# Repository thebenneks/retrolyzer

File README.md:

# RetroLyzer
FPGA Board for a 64-Bit LogicAnalyzer plus a board that allows hacking of a MC68000P10 by plugging it into the logic analyzer board. Thus other Retro CPUs can be hacked :-)

The orginal idea was to build a logicanalyzer and as I came across some retro computing and remembered the fun I had with 68K CPUs I extended the original design by a socket for a MC68000P10 64 DIP. 

The goal is to add bus transceivers for level shifting of the 5V TTL world to the 3.3V LVTTL world that the Spartan 6 can handle. I also add a 512K * 16 Bit SRAM which gets routed through the FPGA and the bus transceivers. 

plus 

using 

resulting into something like this 

# LogicAnalyzer Board

[LogicAnalyzer Details](kicad/logicanalyzer/README.md)

# Retro MC68k-HackingBoard

[MC68000P10 Details](kicad/mc68000board/README.md)

stay tuned .. more to come :-)

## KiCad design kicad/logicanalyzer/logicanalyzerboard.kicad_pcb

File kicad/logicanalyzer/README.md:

# LogicAnalyzer Board 
This folder holds the Kicad project for the PCB

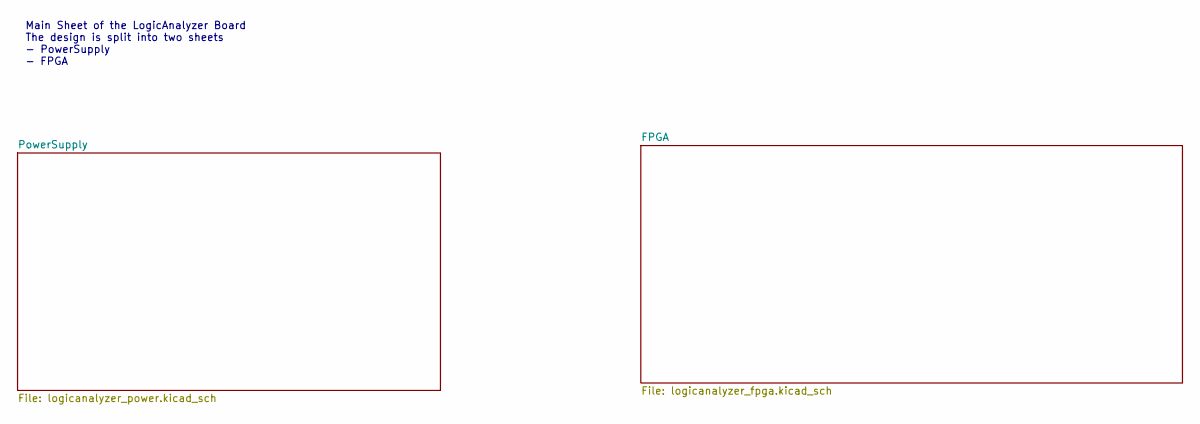
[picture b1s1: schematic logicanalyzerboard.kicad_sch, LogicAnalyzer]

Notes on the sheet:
Main Sheet of the LogicAnalyzer Board The design is split into two sheets - PowerSupply - FPGA

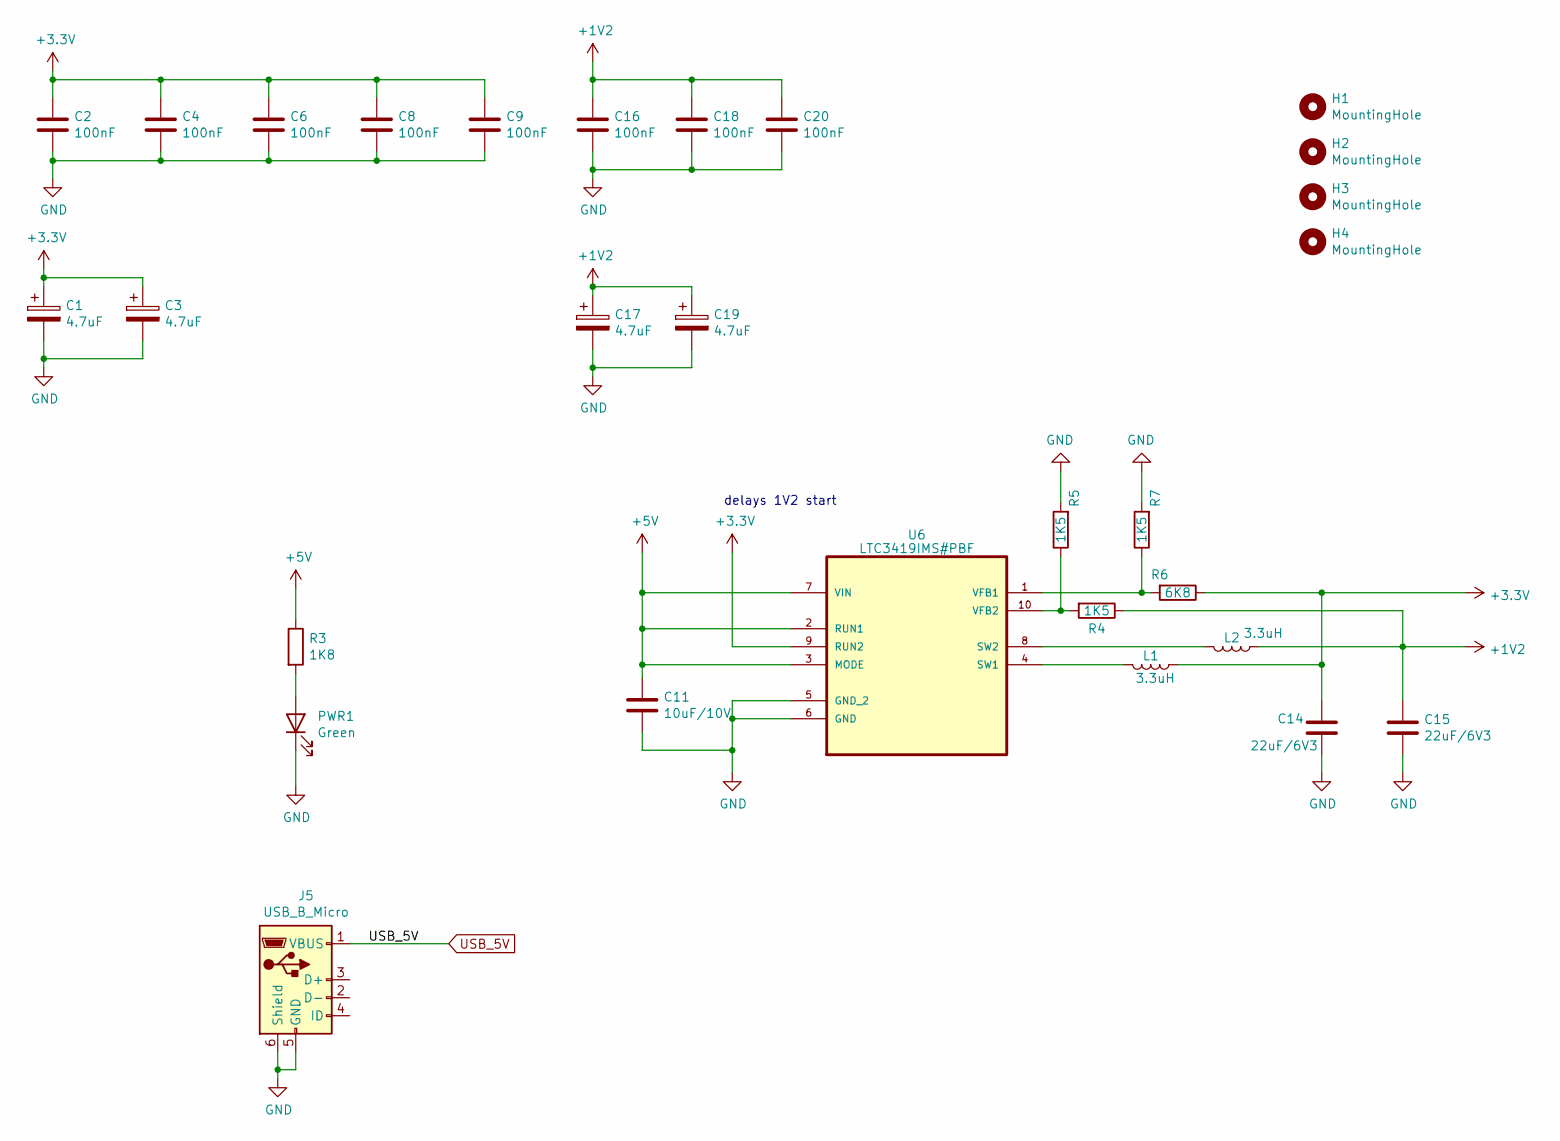
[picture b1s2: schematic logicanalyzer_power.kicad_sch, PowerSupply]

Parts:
C1, C3, C17, C19: 4.7uF; C_0805_2012Metric
C2, C4, C6, C8, C9, C16, C18, C20: 100nF; C_0603_1608Metric
C11: 10uF/10V; C_0805_2012Metric
C14, C15: 22uF/6V3; C_0805_2012Metric
H1, H2, H3, H4: MountingHole; MountingHole3mmInclPaste
J5: USB_B_Micro; USB_Micro-B_Molex-105017-0001
L1, L2: 3.3uH; L_6.3x6.3_H3
PWR1: Green; LED_1206_3216Metric
R3: 1K8; R_0805_2012Metric
R4, R5, R7: 1K5; R_0805_2012Metric
R6: 6K8; R_0805_2012Metric
U6: LTC3419IMS#PBF; SOP50P490X110-10N; MPN LTC3419IMS#PBF

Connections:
+1V2: C15.1, C16.1, C17.1, C18.1, C19.1, C20.1, L2.1, R4.1; also elsewhere on the board
+3V3: C1.1, C2.1, C3.1, C4.1, C6.1, C8.1, C9.1, C14.1, L1.1, R6.1, U6.9 (RUN2); also elsewhere on the board
+5V: C11.1, R3.1, U6.2 (RUN1), U6.3 (MODE), U6.7 (VIN)
GND: C1.2, C2.2, C3.2, C4.2, C6.2, C8.2, C9.2, C11.2, C14.2, C15.2, C16.2, C17.2, C18.2, C19.2, C20.2, J5.5 (GND), J5.6 (Shield), PWR1.1 (K), R5.2, R7.2, U6.5 (GND_2), U6.6 (GND); also elsewhere on the board
unnamed: PWR1.2 (A), R3.2
unnamed: L1.2, U6.4 (SW1)
unnamed: L2.2, U6.8 (SW2)
unnamed: R6.2, R7.1, U6.1 (VFB1)
unnamed: R4.2, R5.1, U6.10 (VFB2)
USB_5V: J5.1 (VBUS)

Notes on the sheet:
delays 1V2 start

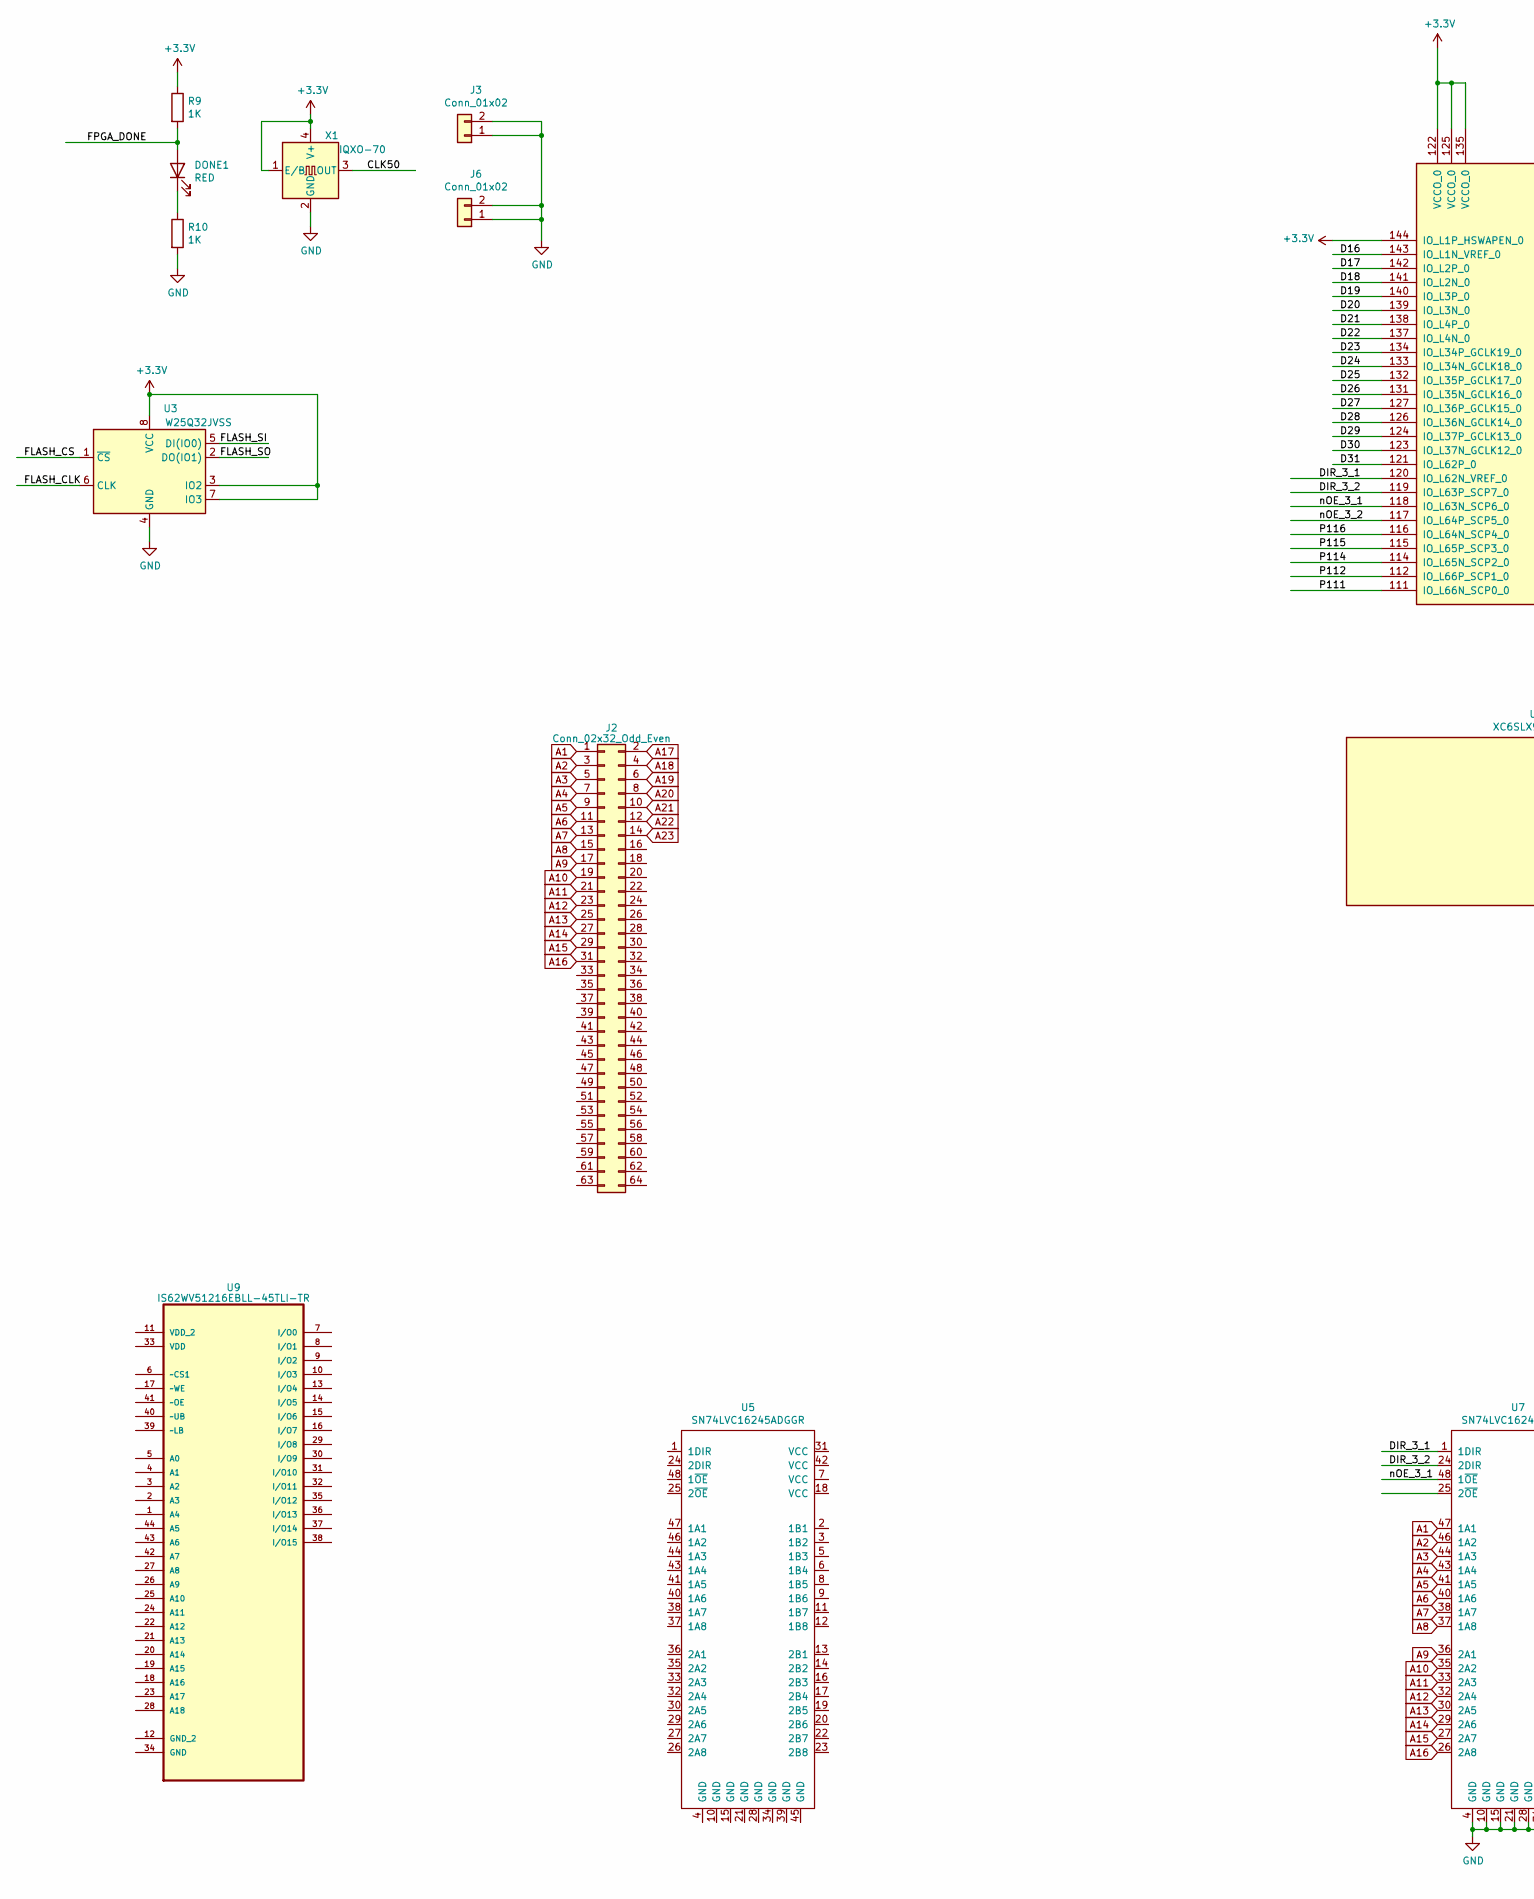
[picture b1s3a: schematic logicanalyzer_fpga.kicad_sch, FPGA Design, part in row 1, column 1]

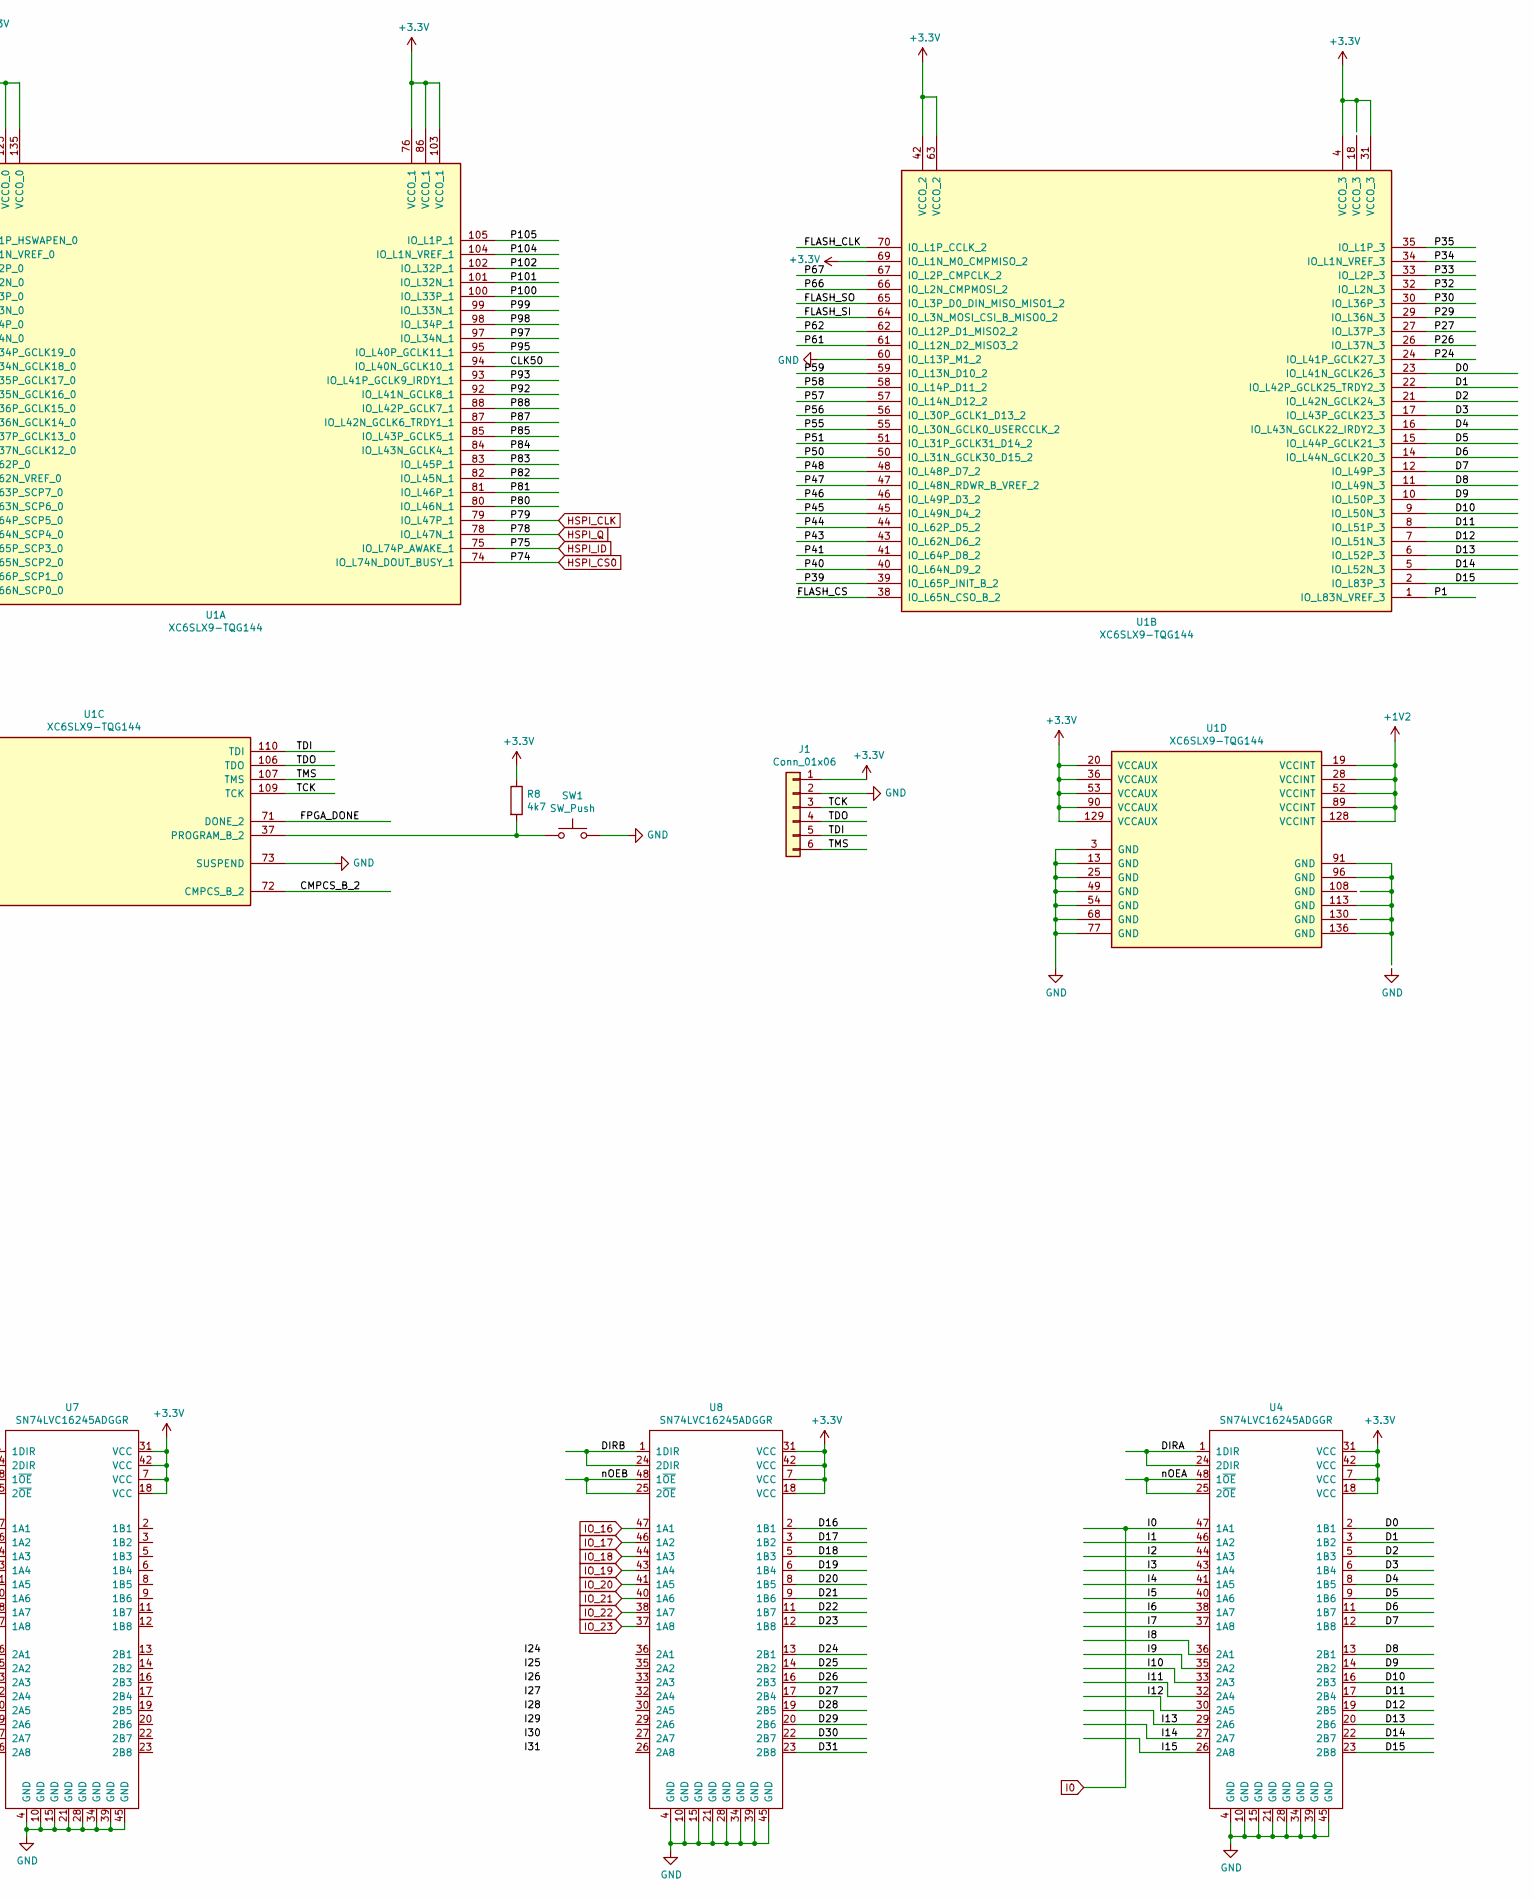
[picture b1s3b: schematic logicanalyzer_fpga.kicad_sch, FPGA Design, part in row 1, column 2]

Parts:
DONE1: RED; LED_1206_3216Metric
J1: Conn_01x06; PinHeader_1x06_P2.54mm_Vertical
J2: Conn_02x32_Odd_Even; PinSocket_2x32_P2.54mm_Vertical
J3, J6: Conn_01x02; PinHeader_1x02_P2.54mm_Vertical
R8: 4k7; R_0805_2012Metric
R9, R10: 1K; R_0805_2012Metric
SW1: SW_Push; SW_DIP_SPSTx01_Slide_6.7x4.1mm_W8.61mm_P2.54mm_LowProfile
U1: XC6SLX9-TQG144; LQFP-144_20x20mm_P0.5mm
U3: W25Q32JVSS; SOIC-8_5.23x5.23mm_P1.27mm
U4, U5, U7, U8: SN74LVC16245ADGGR; TSSOP-48_6.1x12.5mm_P0.5mm
U9: IS62WV51216EBLL-45TLI-TR; IS62WV51216-TSOP-44N; MPN IS62WV51216EBLL-45TLI-TR
X1: IQXO-70; Oscillator_SMD_IQD_IQXO70-4Pin_7.5x5.0mm

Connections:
+1V2: U1.19 (VCCINT), U1.28 (VCCINT), U1.52 (VCCINT), U1.89 (VCCINT), U1.128 (VCCINT); also elsewhere on the board
+3V3: J1.1, R8.1, R9.1, U1.4 (VCCO_3), U1.20 (VCCAUX), U1.31 (VCCO_3), U1.36 (VCCAUX), U1.42 (VCCO_2), U1.53 (VCCAUX), U1.63 (VCCO_2), U1.69 (IO_L1N_M0_CMPMISO_2), U1.76 (VCCO_1), U1.86 (VCCO_1), U1.90 (VCCAUX), U1.103 (VCCO_1), U1.122 (VCCO_0), U1.125 (VCCO_0), U1.129 (VCCAUX), U1.135 (VCCO_0), U1.144 (IO_L1P_HSWAPEN_0), U3.3 (IO2), U3.7 (IO3), U3.8 (VCC), U4.7 (VCC), U4.18 (VCC), U4.31 (VCC), U4.42 (VCC), U7.7 (VCC), U7.18 (VCC), U7.31 (VCC), U7.42 (VCC), U8.7 (VCC), U8.18 (VCC), U8.31 (VCC), U8.42 (VCC), X1.1 (E/B), X1.4 (V+); also elsewhere on the board
/FPGA/CLK50: U1.94 (IO_L40N_GCLK10_1), X1.3 (OUT)
/FPGA/CMPCS_B_2: U1.72 (CMPCS_B_2)
/FPGA/D0: U1.23 (IO_L41N_GCLK26_3), U4.2 (1B1)
/FPGA/D1: U1.22 (IO_L42P_GCLK25_TRDY2_3), U4.3 (1B2)
/FPGA/D2: U1.21 (IO_L42N_GCLK24_3), U4.5 (1B3)
/FPGA/D3: U1.17 (IO_L43P_GCLK23_3), U4.6 (1B4)
/FPGA/D4: U1.16 (IO_L43N_GCLK22_IRDY2_3), U4.8 (1B5)
/FPGA/D5: U1.15 (IO_L44P_GCLK21_3), U4.9 (1B6)
/FPGA/D6: U1.14 (IO_L44N_GCLK20_3), U4.11 (1B7)
/FPGA/D7: U1.12 (IO_L49P_3), U4.12 (1B8)
/FPGA/D8: U1.11 (IO_L49N_3), U4.13 (2B1)
/FPGA/D9: U1.10 (IO_L50P_3), U4.14 (2B2)
/FPGA/D10: U1.9 (IO_L50N_3), U4.16 (2B3)
/FPGA/D11: U1.8 (IO_L51P_3), U4.17 (2B4)
/FPGA/D12: U1.7 (IO_L51N_3), U4.19 (2B5)
/FPGA/D13: U1.6 (IO_L52P_3), U4.20 (2B6)
/FPGA/D14: U1.5 (IO_L52N_3), U4.22 (2B7)
/FPGA/D15: U1.2 (IO_L83P_3), U4.23 (2B8)
/FPGA/D16: U1.143 (IO_L1N_VREF_0), U8.2 (1B1)
/FPGA/D17: U1.142 (IO_L2P_0), U8.3 (1B2)
/FPGA/D18: U1.141 (IO_L2N_0), U8.5 (1B3)
/FPGA/D19: U1.140 (IO_L3P_0), U8.6 (1B4)
/FPGA/D20: U1.139 (IO_L3N_0), U8.8 (1B5)
/FPGA/D21: U1.138 (IO_L4P_0), U8.9 (1B6)
/FPGA/D22: U1.137 (IO_L4N_0), U8.11 (1B7)
/FPGA/D23: U1.134 (IO_L34P_GCLK19_0), U8.12 (1B8)
/FPGA/D24: U1.133 (IO_L34N_GCLK18_0), U8.13 (2B1)
/FPGA/D25: U1.132 (IO_L35P_GCLK17_0), U8.14 (2B2)
/FPGA/D26: U1.131 (IO_L35N_GCLK16_0), U8.16 (2B3)
/FPGA/D27: U1.127 (IO_L36P_GCLK15_0), U8.17 (2B4)
/FPGA/D28: U1.126 (IO_L36N_GCLK14_0), U8.19 (2B5)
/FPGA/D29: U1.124 (IO_L37P_GCLK13_0), U8.20 (2B6)
/FPGA/D30: U1.123 (IO_L37N_GCLK12_0), U8.22 (2B7)
/FPGA/D31: U1.121 (IO_L62P_0), U8.23 (2B8)
/FPGA/DIRA: U4.1 (1DIR), U4.24 (2DIR)
/FPGA/DIRB: U8.1 (1DIR), U8.24 (2DIR)
/FPGA/DIR_3_1: U1.120 (IO_L62N_VREF_0), U7.1 (1DIR)
/FPGA/DIR_3_2: U1.119 (IO_L63P_SCP7_0), U7.24 (2DIR)
/FPGA/FLASH_CLK: U1.70 (IO_L1P_CCLK_2), U3.6 (CLK)
/FPGA/FLASH_CS: U1.38 (IO_L65N_CSO_B_2), U3.1 (~CS)
/FPGA/FLASH_SI: U1.64 (IO_L3N_MOSI_CSI_B_MISO0_2), U3.5 (DI(IO0))
/FPGA/FLASH_SO: U1.65 (IO_L3P_D0_DIN_MISO_MISO1_2), U3.2 (DO(IO1))
/FPGA/FPGA_DONE: DONE1.2 (A), R9.2, U1.71 (DONE_2)
/FPGA/I1: U4.46 (1A2)
/FPGA/I2: U4.44 (1A3)
/FPGA/I3: U4.43 (1A4)
/FPGA/I4: U4.41 (1A5)
/FPGA/I5: U4.40 (1A6)
/FPGA/I6: U4.38 (1A7)
/FPGA/I7: U4.37 (1A8)
/FPGA/I8: U4.36 (2A1)
/FPGA/I9: U4.35 (2A2)
/FPGA/I10: U4.33 (2A3)
/FPGA/I11: U4.32 (2A4)
/FPGA/I12: U4.30 (2A5)
/FPGA/I13: U4.29 (2A6)
/FPGA/I14: U4.27 (2A7)
/FPGA/I15: U4.26 (2A8)
/FPGA/P1: U1.1 (IO_L83N_VREF_3)
/FPGA/P24: U1.24 (IO_L41P_GCLK27_3)
/FPGA/P26: U1.26 (IO_L37N_3)
/FPGA/P27: U1.27 (IO_L37P_3)
/FPGA/P29: U1.29 (IO_L36N_3)
/FPGA/P30: U1.30 (IO_L36P_3)
/FPGA/P32: U1.32 (IO_L2N_3)
/FPGA/P33: U1.33 (IO_L2P_3)
/FPGA/P34: U1.34 (IO_L1N_VREF_3)
/FPGA/P35: U1.35 (IO_L1P_3)
/FPGA/P39: U1.39 (IO_L65P_INIT_B_2)
/FPGA/P40: U1.40 (IO_L64N_D9_2)
/FPGA/P41: U1.41 (IO_L64P_D8_2)
/FPGA/P43: U1.43 (IO_L62N_D6_2)
/FPGA/P44: U1.44 (IO_L62P_D5_2)
/FPGA/P45: U1.45 (IO_L49N_D4_2)
/FPGA/P46: U1.46 (IO_L49P_D3_2)
/FPGA/P47: U1.47 (IO_L48N_RDWR_B_VREF_2)
/FPGA/P48: U1.48 (IO_L48P_D7_2)
/FPGA/P50: U1.50 (IO_L31N_GCLK30_D15_2)
/FPGA/P51: U1.51 (IO_L31P_GCLK31_D14_2)
/FPGA/P55: U1.55 (IO_L30N_GCLK0_USERCCLK_2)
/FPGA/P56: U1.56 (IO_L30P_GCLK1_D13_2)
/FPGA/P57: U1.57 (IO_L14N_D12_2)
/FPGA/P58: U1.58 (IO_L14P_D11_2)
/FPGA/P59: U1.59 (IO_L13N_D10_2)
/FPGA/P61: U1.61 (IO_L12N_D2_MISO3_2)
/FPGA/P62: U1.62 (IO_L12P_D1_MISO2_2)
/FPGA/P66: U1.66 (IO_L2N_CMPMOSI_2)
/FPGA/P67: U1.67 (IO_L2P_CMPCLK_2)
/FPGA/P80: U1.80 (IO_L46N_1)
/FPGA/P81: U1.81 (IO_L46P_1)
/FPGA/P82: U1.82 (IO_L45N_1)
/FPGA/P83: U1.83 (IO_L45P_1)
/FPGA/P84: U1.84 (IO_L43N_GCLK4_1)
/FPGA/P85: U1.85 (IO_L43P_GCLK5_1)
/FPGA/P87: U1.87 (IO_L42N_GCLK6_TRDY1_1)
/FPGA/P88: U1.88 (IO_L42P_GCLK7_1)
/FPGA/P92: U1.92 (IO_L41N_GCLK8_1)
/FPGA/P93: U1.93 (IO_L41P_GCLK9_IRDY1_1)
/FPGA/P95: U1.95 (IO_L40P_GCLK11_1)
/FPGA/P97: U1.97 (IO_L34N_1)
/FPGA/P98: U1.98 (IO_L34P_1)
/FPGA/P99: U1.99 (IO_L33N_1)
/FPGA/P100: U1.100 (IO_L33P_1)
/FPGA/P101: U1.101 (IO_L32N_1)
/FPGA/P102: U1.102 (IO_L32P_1)
/FPGA/P104: U1.104 (IO_L1N_VREF_1)
/FPGA/P105: U1.105 (IO_L1P_1)
/FPGA/P111: U1.111 (IO_L66N_SCP0_0)
/FPGA/P112: U1.112 (IO_L66P_SCP1_0)
/FPGA/P114: U1.114 (IO_L65N_SCP2_0)
/FPGA/P115: U1.115 (IO_L65P_SCP3_0)
/FPGA/P116: U1.116 (IO_L64N_SCP4_0)
/FPGA/TCK: J1.3, U1.109 (TCK)
/FPGA/TDI: J1.5, U1.110 (TDI)
/FPGA/TDO: J1.4, U1.106 (TDO)
/FPGA/TMS: J1.6, U1.107 (TMS)
/FPGA/nOEA: U4.25 (2~OE), U4.48 (1~OE)
/FPGA/nOEB: U8.25 (2~OE), U8.48 (1~OE)
/FPGA/nOE_3_1: U1.118 (IO_L63N_SCP6_0), U7.48 (1~OE)
/FPGA/nOE_3_2: U1.117 (IO_L64P_SCP5_0)
A1: J2.1, U7.47 (1A1)
A2: J2.3, U7.46 (1A2)
A3: J2.5, U7.44 (1A3)
A4: J2.7, U7.43 (1A4)
A5: J2.9, U7.41 (1A5)
A6: J2.11, U7.40 (1A6)
A7: J2.13, U7.38 (1A7)
A8: J2.15, U7.37 (1A8)
A9: J2.17, U7.36 (2A1)
A10: J2.19, U7.35 (2A2)
A11: J2.21, U7.33 (2A3)
A12: J2.23, U7.32 (2A4)
A13: J2.25, U7.30 (2A5)
A14: J2.27, U7.29 (2A6)
A15: J2.29, U7.27 (2A7)
A16: J2.31, U7.26 (2A8)
A17: J2.2
A18: J2.4
A19: J2.6
A20: J2.8
A21: J2.10
A22: J2.12
A23: J2.14
GND: J1.2, J3.1, J3.2, J6.1, J6.2, R10.2, SW1.2, U1.3 (GND), U1.13 (GND), U1.25 (GND), U1.49 (GND), U1.54 (GND), U1.60 (IO_L13P_M1_2), U1.68 (GND), U1.73 (SUSPEND), U1.77 (GND), U3.4 (GND), U4.4 (GND), U4.10 (GND), U4.15 (GND), U4.21 (GND), U4.28 (GND), U4.34 (GND), U4.39 (GND), U4.45 (GND), U7.4 (GND), U7.10 (GND), U7.15 (GND), U7.21 (GND), U7.28 (GND), U7.34 (GND), U7.39 (GND), U7.45 (GND), U8.4 (GND), U8.10 (GND), U8.15 (GND), U8.21 (GND), U8.28 (GND), U8.34 (GND), U8.39 (GND), U8.45 (GND), X1.2 (GND); also elsewhere on the board
HSPI_CLK: U1.79 (IO_L47P_1)
HSPI_CS0: U1.74 (IO_L74N_DOUT_BUSY_1)
HSPI_ID: U1.75 (IO_L74P_AWAKE_1)
HSPI_Q: U1.78 (IO_L47N_1)
I0: U4.47 (1A1)
IO_16: U8.47 (1A1)
IO_17: U8.46 (1A2)
IO_18: U8.44 (1A3)
IO_19: U8.43 (1A4)
IO_20: U8.41 (1A5)
IO_21: U8.40 (1A6)
IO_22: U8.38 (1A7)
IO_23: U8.37 (1A8)
unnamed: DONE1.1 (K), R10.1
unnamed: R8.2, SW1.1, U1.37 (PROGRAM_B_2)
unnamed: U1.91 (GND), U1.96 (GND), U1.113 (GND), U1.136 (GND)

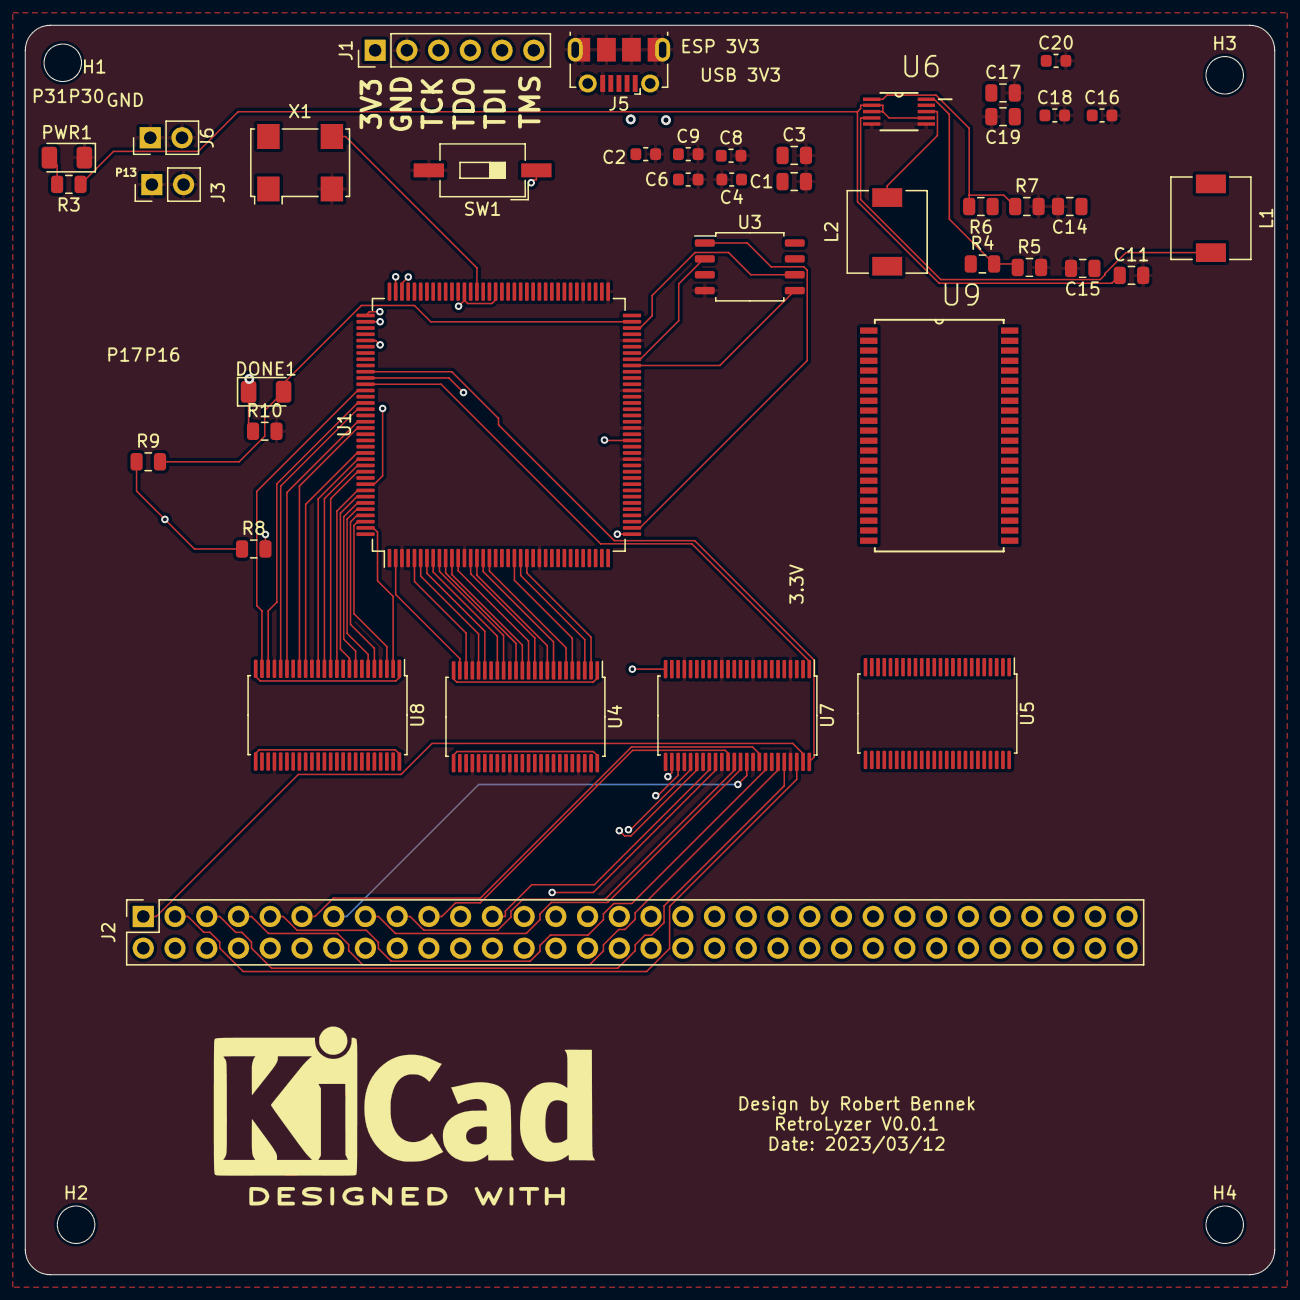
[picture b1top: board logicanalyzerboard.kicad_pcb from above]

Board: 4 copper layers, 100.0 x 100.0 mm, 46 parts (0 on the bottom side), 77 nets.

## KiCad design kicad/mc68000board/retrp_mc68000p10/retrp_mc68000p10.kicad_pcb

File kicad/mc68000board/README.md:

# MC68000P10 Board
This folder holds the Kicad project for a dedicated PCB board that can be plugged into the logic analyzer board

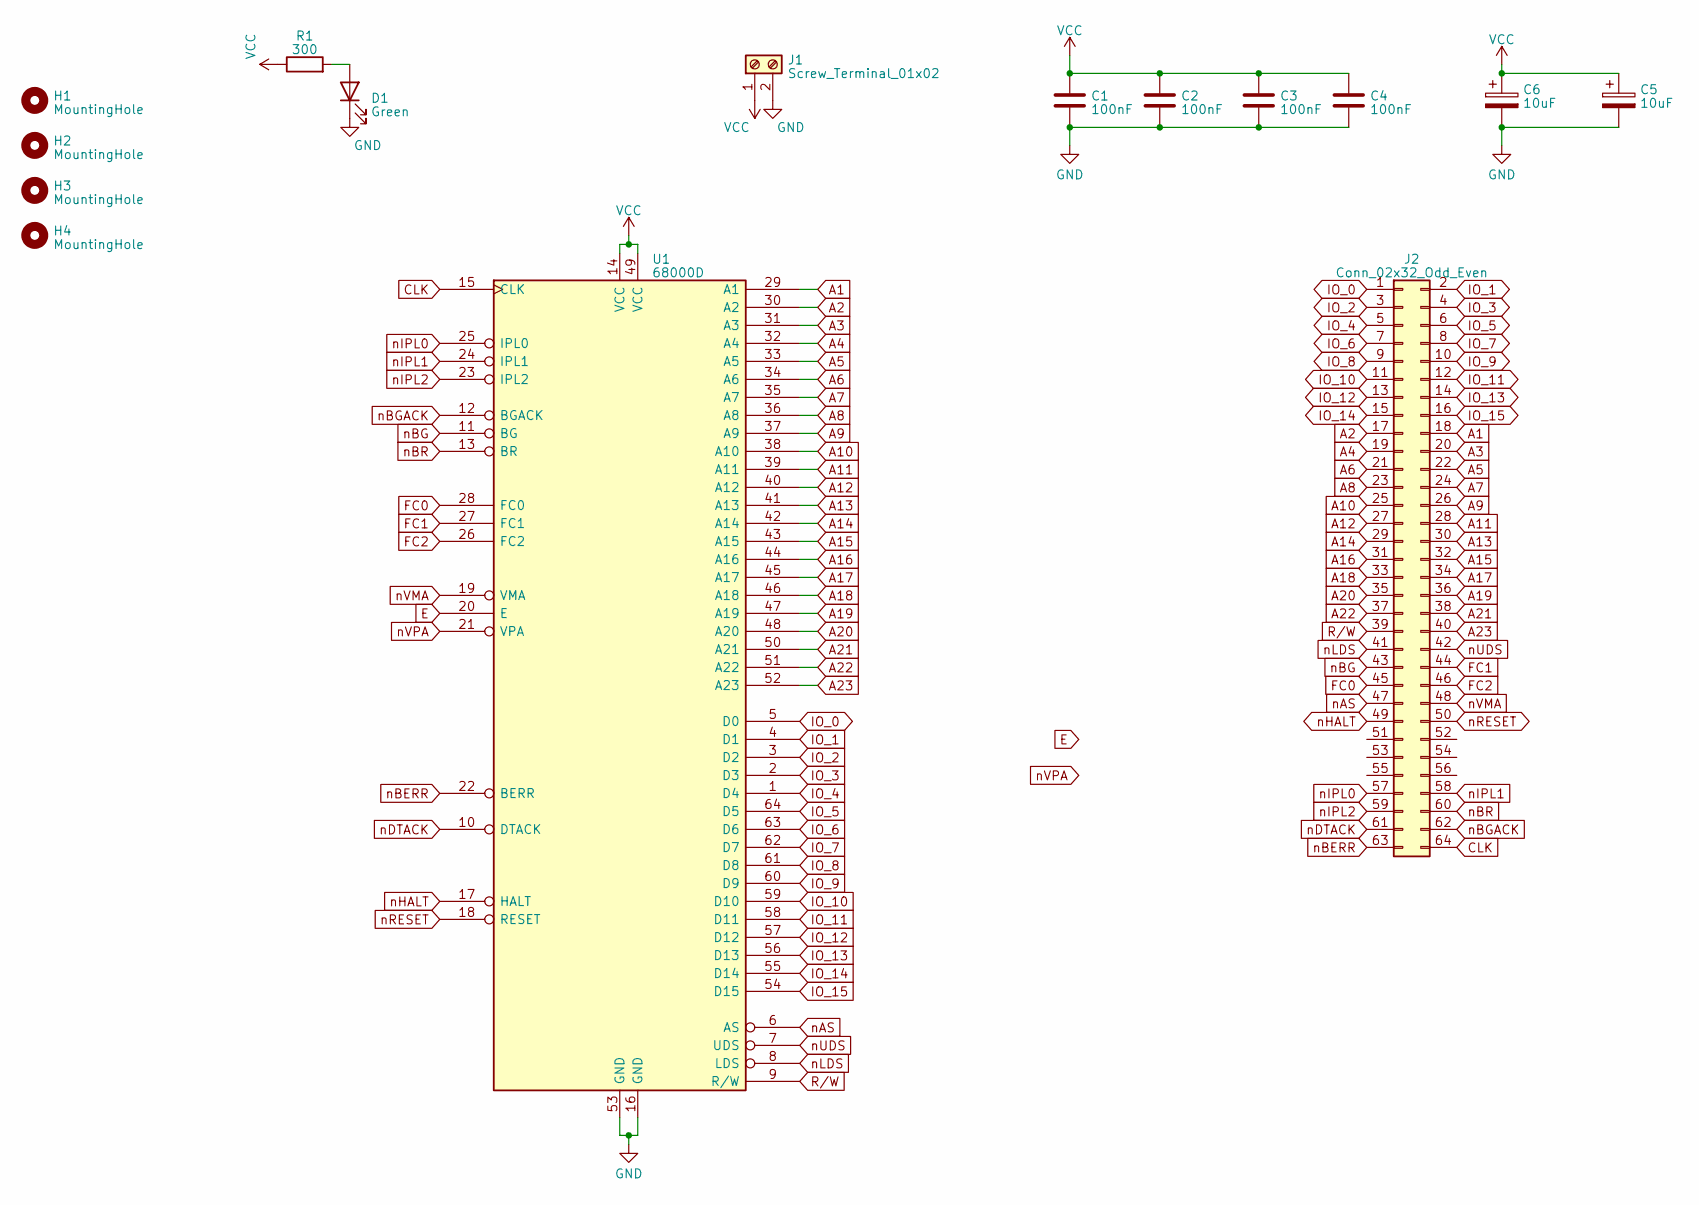
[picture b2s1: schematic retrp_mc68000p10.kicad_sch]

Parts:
C1, C2, C3, C4: 100nF; C_0805_2012Metric
C5, C6: 10uF; CP_Elec_6.3x5.3
D1: Green; D_0805_2012Metric
H1, H2, H3, H4: MountingHole; MountingHole_3mm
J1: Screw_Terminal_01x02; TerminalBlock_bornier-2_P5.08mm
J2: Conn_02x32_Odd_Even; PinHeader_2x32_P2.54mm_Horizontal
R1: 300; R_0805_2012Metric
U1: 68000D; DIP-64_W25.4mm

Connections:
A1: J2.18, U1.29 (A1)
A2: J2.17, U1.30 (A2)
A3: J2.20, U1.31 (A3)
A4: J2.19, U1.32 (A4)
A5: J2.22, U1.33 (A5)
A6: J2.21, U1.34 (A6)
A7: J2.24, U1.35 (A7)
A8: J2.23, U1.36 (A8)
A9: J2.26, U1.37 (A9)
A10: J2.25, U1.38 (A10)
A11: J2.28, U1.39 (A11)
A12: J2.27, U1.40 (A12)
A13: J2.30, U1.41 (A13)
A14: J2.29, U1.42 (A14)
A15: J2.32, U1.43 (A15)
A16: J2.31, U1.44 (A16)
A17: J2.34, U1.45 (A17)
A18: J2.33, U1.46 (A18)
A19: J2.36, U1.47 (A19)
A20: J2.35, U1.48 (A20)
A21: J2.38, U1.50 (A21)
A22: J2.37, U1.51 (A22)
A23: J2.40, U1.52 (A23)
CLK: J2.64, U1.15 (CLK)
E: U1.20 (E)
FC0: J2.45, U1.28 (FC0)
FC1: J2.44, U1.27 (FC1)
FC2: J2.46, U1.26 (FC2)
GND: C1.2, C2.2, C3.2, C4.2, C5.2, C6.2, D1.1 (K), J1.2, U1.16 (GND), U1.53 (GND)
IO_0: J2.1, U1.5 (D0)
IO_1: J2.2, U1.4 (D1)
IO_2: J2.3, U1.3 (D2)
IO_3: J2.4, U1.2 (D3)
IO_4: J2.5, U1.1 (D4)
IO_5: J2.6, U1.64 (D5)
IO_6: J2.7, U1.63 (D6)
IO_7: J2.8, U1.62 (D7)
IO_8: J2.9, U1.61 (D8)
IO_9: J2.10, U1.60 (D9)
IO_10: J2.11, U1.59 (D10)
IO_11: J2.12, U1.58 (D11)
IO_12: J2.13, U1.57 (D12)
IO_13: J2.14, U1.56 (D13)
IO_14: J2.15, U1.55 (D14)
IO_15: J2.16, U1.54 (D15)
unnamed: D1.2 (A), R1.2
R/W: J2.39, U1.9 (R/W)
VCC: C1.1, C2.1, C3.1, C4.1, C5.1, C6.1, J1.1, R1.1, U1.14 (VCC), U1.49 (VCC)
nAS: J2.47, U1.6 (AS)
nBERR: J2.63, U1.22 (BERR)
nBG: J2.43, U1.11 (BG)
nBGACK: J2.62, U1.12 (BGACK)
nBR: J2.60, U1.13 (BR)
nDTACK: J2.61, U1.10 (DTACK)
nHALT: J2.49, U1.17 (HALT)
nIPL0: J2.57, U1.25 (IPL0)
nIPL1: J2.58, U1.24 (IPL1)
nIPL2: J2.59, U1.23 (IPL2)
nLDS: J2.41, U1.8 (LDS)
nRESET: J2.50, U1.18 (RESET)
nUDS: J2.42, U1.7 (UDS)
nVMA: J2.48, U1.19 (VMA)
nVPA: U1.21 (VPA)

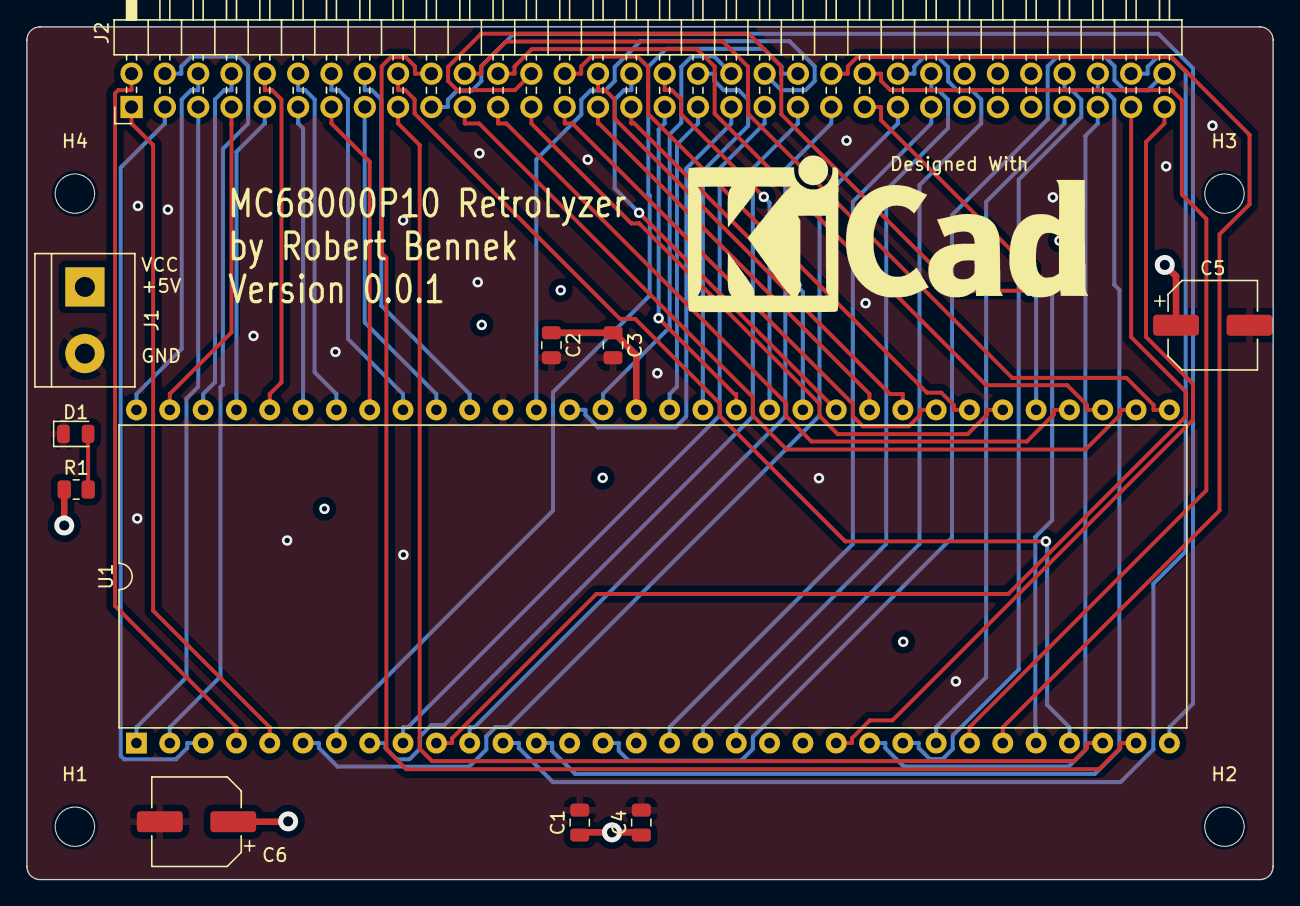
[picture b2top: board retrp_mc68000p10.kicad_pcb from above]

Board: 4 copper layers, 95.0 x 65.0 mm, 15 parts (0 on the bottom side), 61 nets.

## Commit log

2023-03-11 more prosa
2023-03-11 #1 get things started
2023-03-11 #1 typo
2023-03-11 #1 plantuml test
2023-03-11 #1 plantuml test 2
2023-03-11 #1 plantuml test 3
2023-03-11 #1 plantuml test 4
2023-03-11 #1 plantuml test 5
2023-03-11 #1 plantuml test 6
2023-03-11 #1 plantuml test 7
2023-03-11 #1 more stuff
2023-03-11 #1 plus logicanalyzer
2023-03-11 #1 plus spartan 6
2023-03-11 #1 ups typo
2023-03-11 #1 changed my mind
2023-03-12 #1 some cleanup
2023-03-12 #1 adding project folders and content
2023-03-12 #1 more content
2023-03-12 #1 now with working image sizing
2023-03-12 #1 image updated
2023-03-12 #1 no splitted into 2boards
2023-03-12 #1 unlcear if this fixes it
2023-03-12 #1 back to other image ref
2023-03-12 #1 needed one more linefeed
2023-03-12 #1 now with more on top & bottom layer
2023-03-12 #1 now with rendered image
2023-03-12 #1 plus bottom image
2023-03-12 #1 now also the logic board too
2023-03-12 #1 refreshed logic board image
2023-03-12 #1 more pictures
